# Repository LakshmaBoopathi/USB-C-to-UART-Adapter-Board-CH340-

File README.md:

USB-C to UART Adapter Board (CH340)

A compact USB Type-C to UART Adapter Board designed using the CH340 USB-to-Serial converter IC. This board provides a reliable USB-to-TTL serial interface for programming, debugging, and communicating with microcontrollers and embedded systems.

**Features**

    USB Type-C interface for modern connectivity
  
    CH340 USB-to-UART bridge IC
  
    Supports 3.3V and 5V UART communication
  
    TX, RX, VCC, and GND header pins
  
    Power and communication status LEDs
  
    Compact and easy-to-use PCB layout
  
    Designed using KiCad

**Applications**

    STM32 programming and debugging
  
    Arduino and ESP32 serial communication
  
    Bootloader flashing
  
    Embedded system development
  
    Serial console and debugging

**PCB Design Highlights**

      Schematic capture in KiCad
    
      Professional PCB layout
      
      Proper USB differential pair routing
      
      Decoupling capacitors placed near the IC
      
      Ground plane for improved signal integrity
      
      Design Rule Check (DRC) and Electrical Rule Check (ERC) verified
      
**Learning Outcomes****
      
      USB interface design
      
      USB-to-UART communication using CH340
      
      PCB component placement and routing
      
      Power distribution and decoupling techniques
      
      Hardware debugging and PCB design workflow
  
**  Tools Used**
  
      KiCad
      
      CH340 USB-to-UART IC
      
      USB Type-C Connector

This project demonstrates the design of a reliable USB-C to UART adapter suitable for embedded development, firmware flashing, and serial debugging.

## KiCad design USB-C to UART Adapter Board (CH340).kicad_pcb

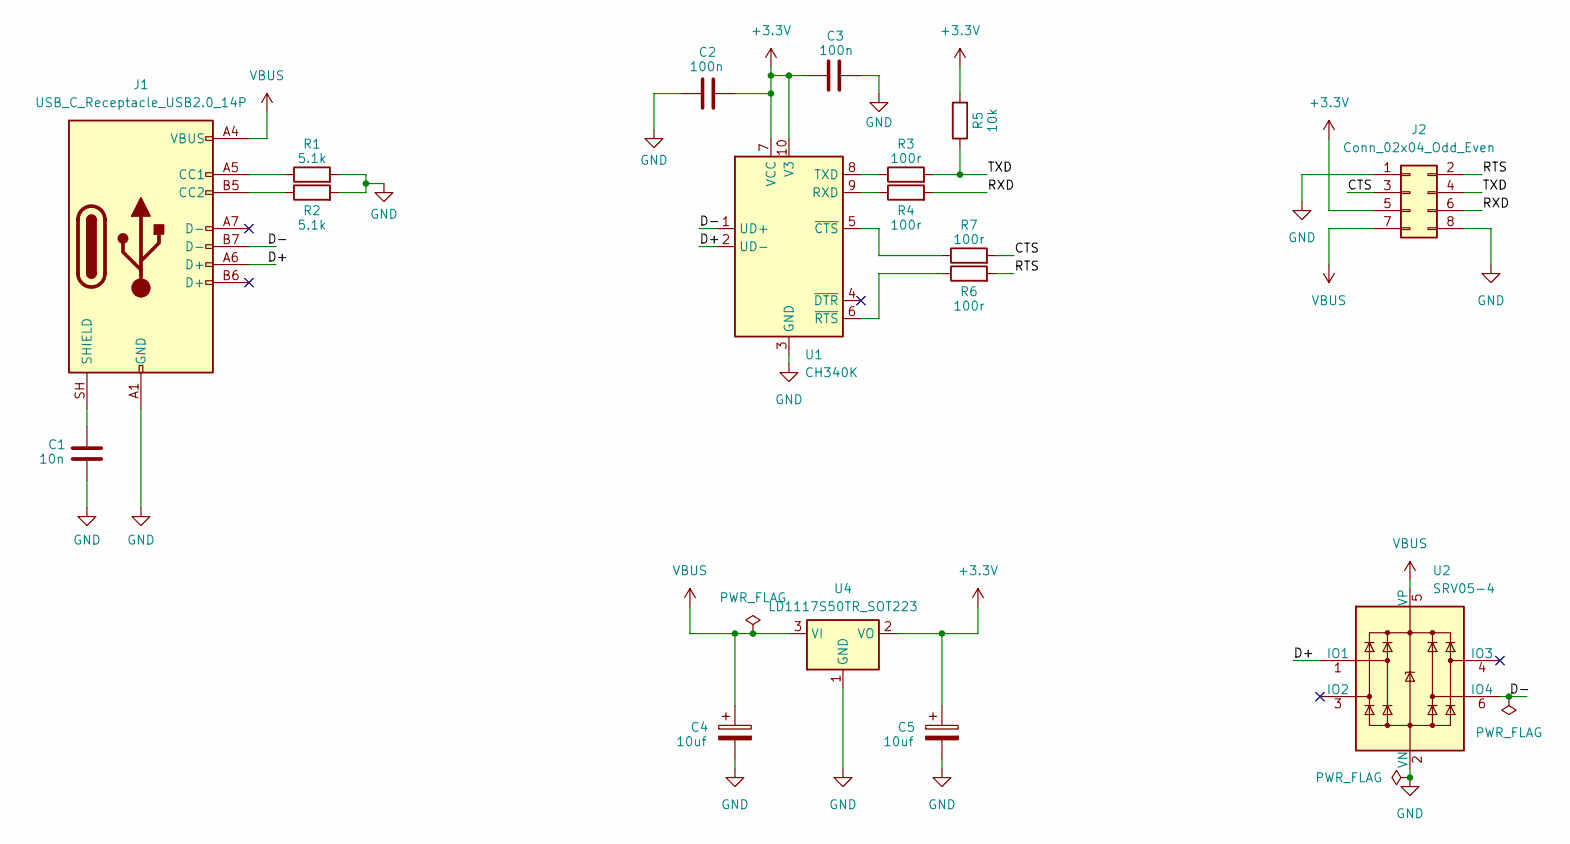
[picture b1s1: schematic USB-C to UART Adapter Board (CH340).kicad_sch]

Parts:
C1: 10n; C_0603_1608Metric
C2, C3: 100n; C_0603_1608Metric
C4, C5: 10uf; C_0805_2012Metric
J1: USB_C_Receptacle_USB2.0_14P; USB_C_Receptacle_HRO_TYPE-C-31-M-12
J2: Conn_02x04_Odd_Even; PinHeader_2x04_P2.54mm_Vertical
R1, R2: 5.1k; R_0603_1608Metric
R3, R4, R6, R7: 100r; R_0603_1608Metric
R5: 10k; R_0603_1608Metric
U1: CH340K; SSOP-10-1EP_3.9x4.9mm_P1mm_EP2.1x3.3mm
U2: SRV05-4; SOT-23-6
U4: LD1117S50TR_SOT223; SOT-223-3_TabPin2

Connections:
+3.3V: C2.2, C3.1, C5.1, J2.5, R5.2, U1.7 (VCC), U1.10 (V3), U4.2 (VO)
/CTS: J2.3, R7.2
/D+: J1.A6 (D+), U1.2 (UD-), U2.1 (IO1)
/D-: J1.B7 (D-), U1.1 (UD+), U2.6 (IO4)
/RTS: J2.2, R6.2
/RXD: J2.6, R4.2
/TXD: J2.4, R3.2, R5.1
GND: C1.2, C2.1, C3.2, C4.2, C5.2, J1.A1 (GND), J1.A12 (GND), J1.B1 (GND), J1.B12 (GND), J2.1, J2.8, R1.2, R2.2, U1.3 (GND), U1.11 (GND), U2.2 (VN), U4.1 (GND)
unnamed: J1.A5 (CC1), R1.1
unnamed: J1.B5 (CC2), R2.1
unnamed: C1.1, J1.SH (SHIELD)
unnamed: R4.1, U1.9 (RXD)
unnamed: R3.1, U1.8 (TXD)
unnamed: R7.1, U1.5 (~CTS)
unnamed: R6.1, U1.6 (~RTS)
VBUS: C4.1, J1.A4 (VBUS), J1.A9 (VBUS), J1.B4 (VBUS), J1.B9 (VBUS), J2.7, U2.5 (VP), U4.3 (VI)

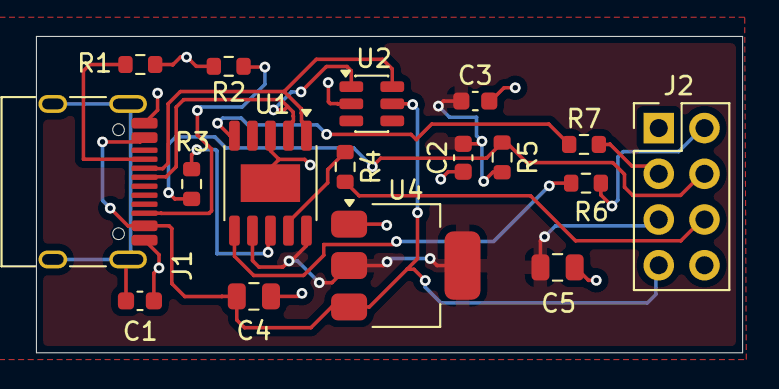
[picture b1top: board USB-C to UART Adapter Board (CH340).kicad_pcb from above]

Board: 2 copper layers, 39.2 x 17.6 mm, 17 parts (0 on the bottom side), 16 nets.
